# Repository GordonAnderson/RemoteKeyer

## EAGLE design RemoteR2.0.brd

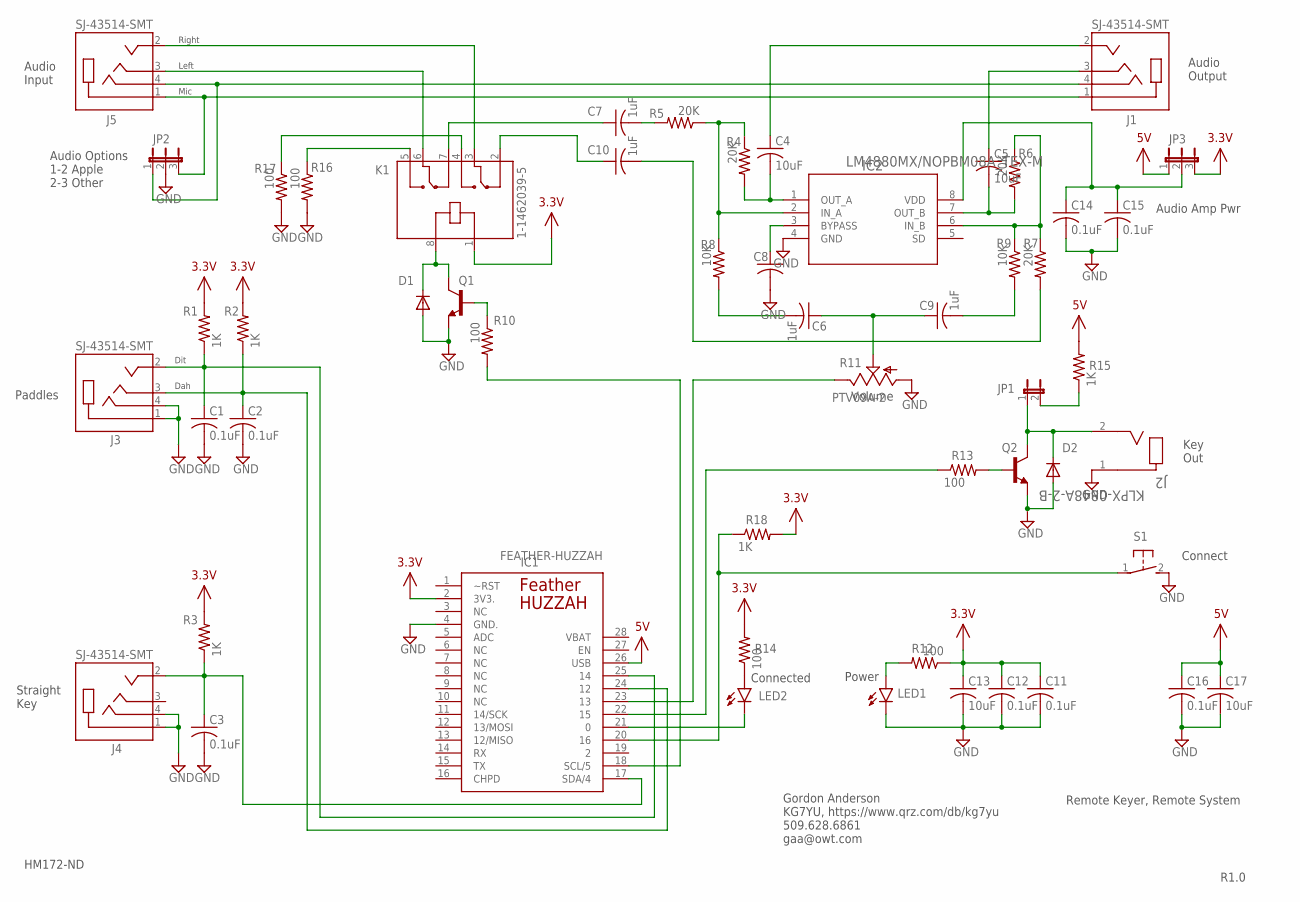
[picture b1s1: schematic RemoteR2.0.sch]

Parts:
C1, C2, C3, C11, C12, C14, C15, C16: 0.1uF; C0805
C4, C5: 10uF; C1206
C6, C7, C9, C10: 1uF; C0805
C8: C-USC0805; C0805
C13, C17: 10uF; C0805
D1, D2: DIODE-SOD323-R; SOD323-R
IC1: FEATHER-HUZZAH
IC2: LM4880MX/NOPBM08A_TEX-M; M08A_TEX-M
J1, J3, J4, J5: SJ-43514-SMT; CUI_SJ-43514-SMT
J2: KLPX-0848A-2-B; KLPX-0848A-2-B_KYC
JP1: JP1E; JP1
JP2, JP3: JP2E; JP2
K1: 1-1462039-5; RELAY_1-1462039-5
LED1, LED2: LED5MM
Q1, Q2: MMBT2369LT1-NPN-SOT23-BEC; SOT23-BEC
R1, R2, R3, R15, R18: 1K; R0805
R4, R5, R6, R7: 20K; R0805
R8, R9: 10K; R0805
R10, R12, R13, R14: 100; R0805
R11: PTV09A-2
R16, R17: 100; R1206
S1: 31-XX; B3F-31XX

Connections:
3.3V: C11.1, C12.1, C13.1, IC1.2 (3V3.), JP3.3, K1.1, R1.2, R2.2, R3.2, R12.1, R14.2, R18.2
5V: C16.1, C17.1, IC1.26 (USB), JP3.1, R15.2
CHPD: IC1.16 (CHPD)
GND: C1.2, C2.2, C3.2, C8.2, C11.2, C12.2, C13.2, C14.2, C15.2, C16.2, C17.2, D1.A, D2.A, IC1.4 (GND.), IC2.4 (GND), J2.1, J3.1 (SLEEVE), J3.4 (RING2), J4.1 (SLEEVE), J4.4 (RING2), JP2.2, LED1.K (C), Q1.E, Q2.E, R11.1 (A), R16.2, R17.2, S1.2 (S)
unnamed: Q2.B, R13.2
unnamed: C2.1, IC1.24 (12), J3.3 (RING1), R2.1
unnamed: C3.1, IC1.17 (SDA/4), J4.2 (TIP), R3.1
unnamed: C1.1, IC1.25 (14), J3.2 (TIP), R1.1
unnamed: C9.2, R9.2
unnamed: C4.2, IC2.1 (OUT_A), R4.2
unnamed: IC2.2 (IN_A), R4.1, R5.1, R8.1
unnamed: C8.1, IC2.3 (BYPASS)
unnamed: C7.1, K1.7
unnamed: C6.2, R8.2
unnamed: C5.2, IC2.7 (OUT_B), R6.2
unnamed: IC2.6 (IN_B), R6.1, R7.1, R9.1
unnamed: C6.1, C9.1, R11.2 (S)
unnamed: Q1.B, R10.1
unnamed: C4.1, J1.2 (TIP)
unnamed: C5.1, J1.3 (RING1)
unnamed: J5.3 (RING1), K1.6
unnamed: J5.2 (TIP), K1.3
unnamed: J1.1 (SLEEVE), J5.1 (SLEEVE), JP2.3
unnamed: C7.2, R5.2
unnamed: C10.1, K1.2
unnamed: C10.2, R7.2
unnamed: LED1.A, R12.2
unnamed: LED2.A, R14.1
unnamed: IC1.21 (0), LED2.K (C)
unnamed: IC1.23 (13), R11.3 (E)
unnamed: IC1.22 (15), R13.1
unnamed: IC1.18 (SCL/5), R10.2
unnamed: JP1.2, R15.1
unnamed: K1.4, R17.1
unnamed: K1.5, R16.1
unnamed: IC1.20 (16), R18.1, S1.1
unnamed: C14.1, C15.1, IC2.8 (VDD), JP3.2
unnamed: J1.4 (RING2), J5.4 (RING2), JP2.1
RELAY-: D2.C, J2.2, JP1.1, Q2.C
RELAY-1: D1.C, K1.8, Q1.C
VBAT: IC1.28 (VBAT)

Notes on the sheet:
Paddles
Straight Key
Right
Left
Mic
Dit
Dah
Power
Connected
Audio Input
Audio Output
Key Out
Volume
Remote Keyer, Remote System
R1.0
Connect
HM172-ND
Audio Amp Pwr
Audio Options 1-2 Apple 2-3 Other
Gordon Anderson KG7YU, https://www.qrz.com/db/kg7yu 509.628.6861 gaa@owt.com

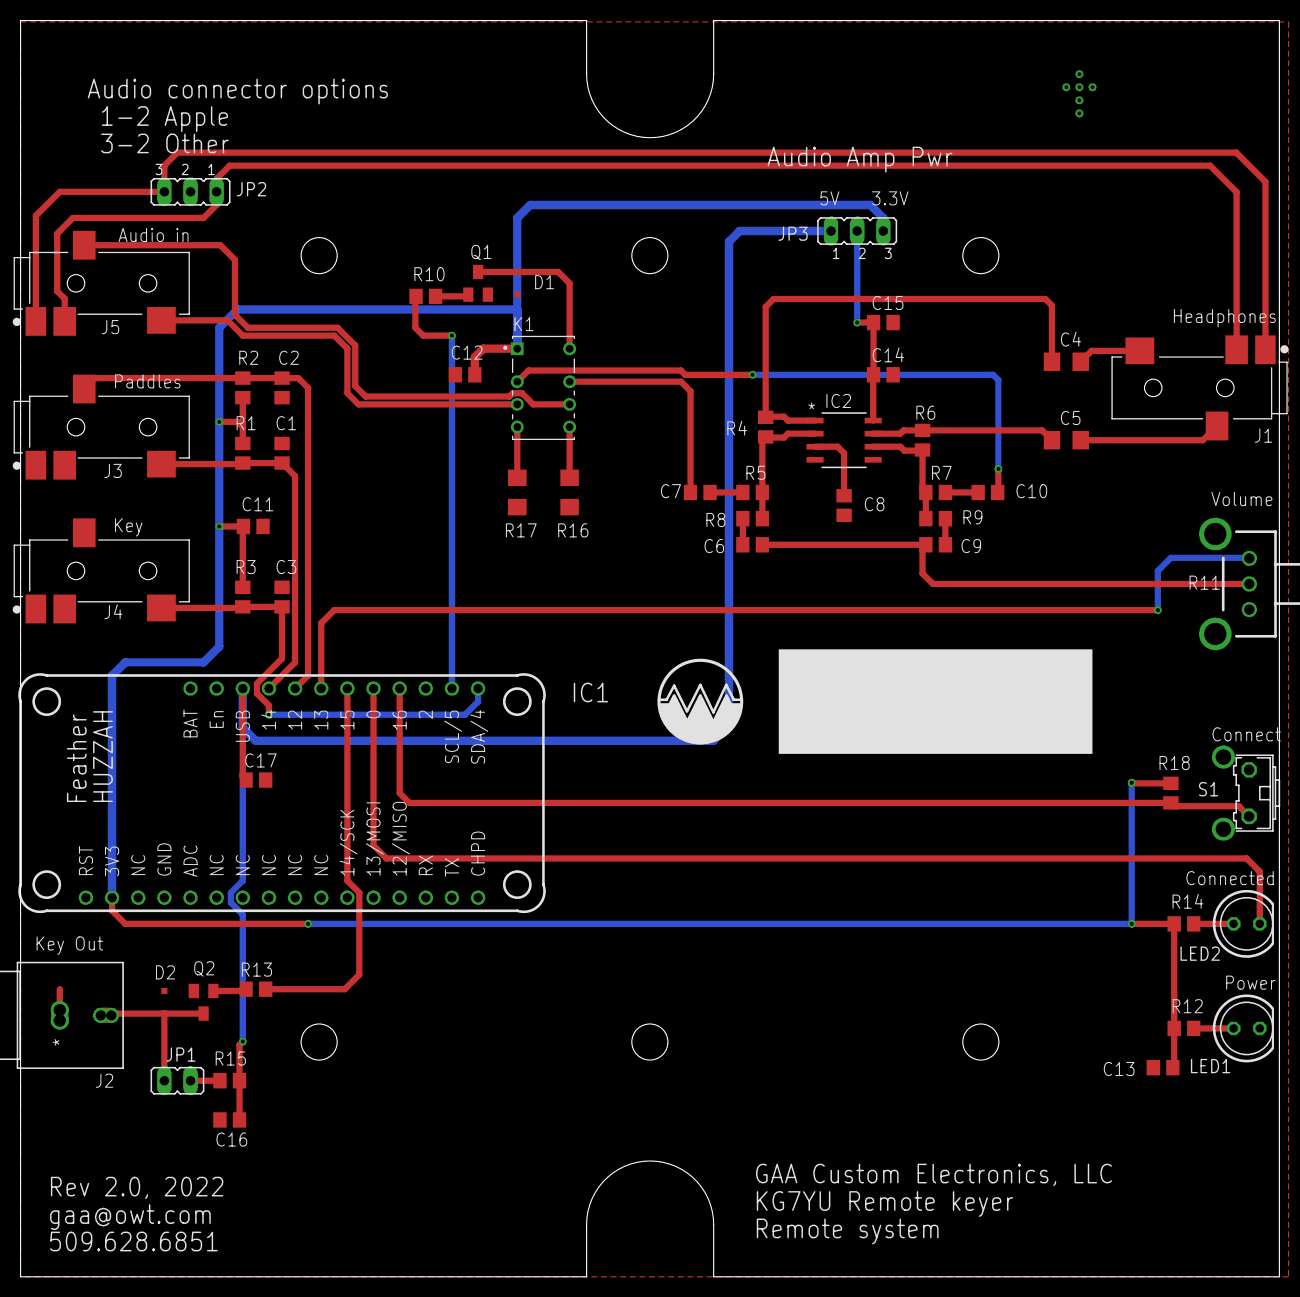
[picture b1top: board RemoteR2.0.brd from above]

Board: 2 copper layers, 122.3 x 122.0 mm, 54 parts (0 on the bottom side), 39 nets.

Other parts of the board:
U$1: LOGO2

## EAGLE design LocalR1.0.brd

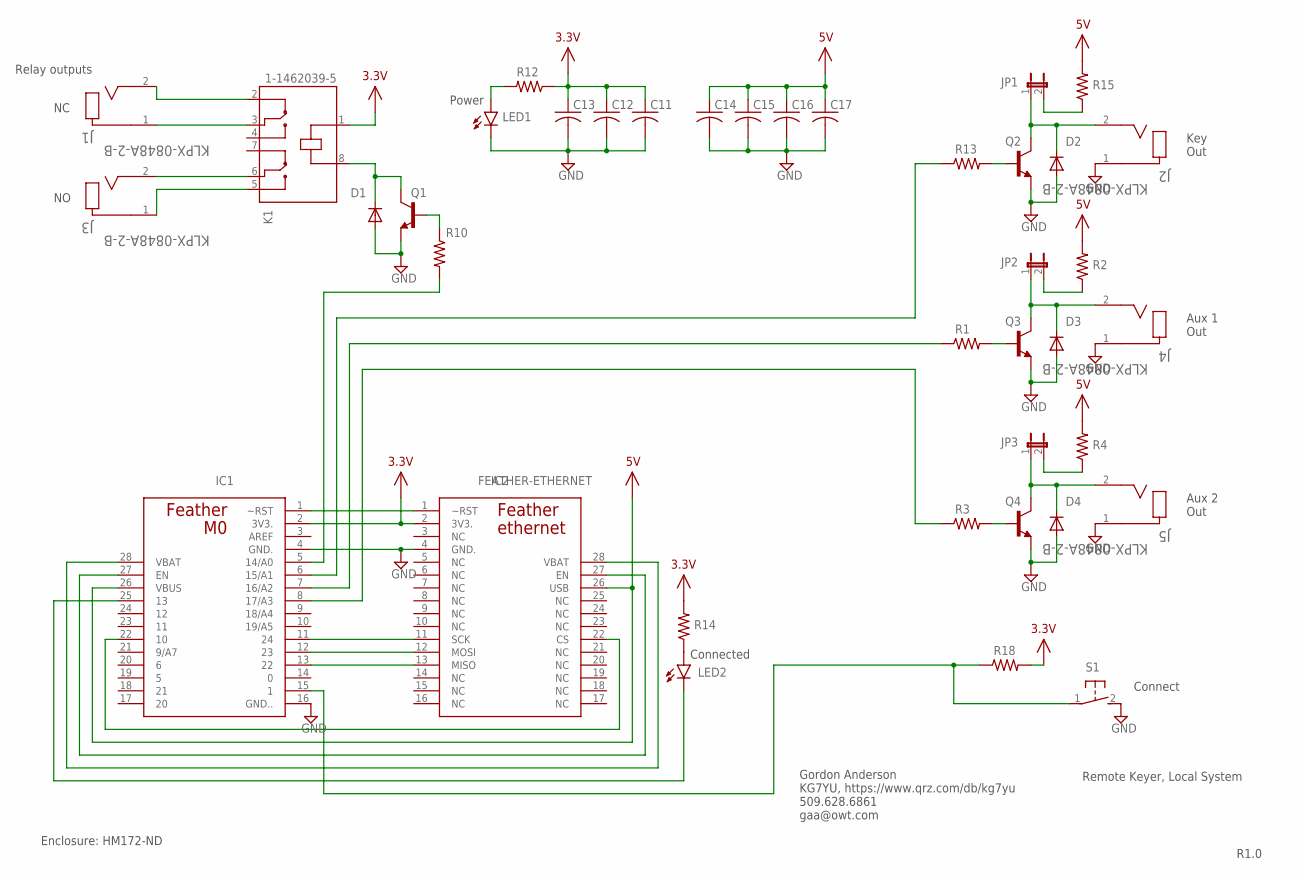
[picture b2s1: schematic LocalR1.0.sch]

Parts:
C11, C12, C13, C14, C15, C16, C17: C-USC0805; C0805
D1, D2, D3, D4: DIODE-SOD323-R; SOD323-R
IC1: FEATHER-M0
IC2: FEATHER-ETHERNET
J1, J2, J3, J4, J5: KLPX-0848A-2-B; KLPX-0848A-2-B_KYC
JP1, JP2, JP3: JP1E; JP1
K1: 1-1462039-5; RELAY_1-1462039-5
LED1, LED2: LED5MM
Q1, Q2, Q3, Q4: MMBT2369LT1-NPN-SOT23-BEC; SOT23-BEC
R1, R2, R3, R4, R10, R12, R13, R14, R15, R18: R-US_R0805; R0805
S1: 31-XX; B3F-31XX

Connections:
3.3V: C11.1, C12.1, C13.1, IC1.2 (3V3.), IC2.2 (3V3.), K1.1, R12.1, R14.2, R18.2
5V: C14.1, C15.1, C16.1, C17.1, IC1.26 (VBUS), IC2.26 (USB), R2.2, R4.2, R15.2
GND: C11.2, C12.2, C13.2, C14.2, C15.2, C16.2, C17.2, D1.A, D2.A, D3.A, D4.A, IC1.4 (GND.), IC1.16 (GND..), IC2.4 (GND.), J2.1, J4.1, J5.1, LED1.K (C), Q1.E, Q2.E, Q3.E, Q4.E, S1.2 (S)
unnamed: Q2.B, R13.2
unnamed: J1.1, K1.3
unnamed: J1.2, K1.2
unnamed: J3.2, K1.6
unnamed: J3.1, K1.5
unnamed: Q3.B, R1.2
unnamed: JP2.2, R2.1
unnamed: Q4.B, R3.2
unnamed: JP3.2, R4.1
unnamed: IC1.13 (22), IC2.13 (MISO)
unnamed: IC1.12 (23), IC2.12 (MOSI)
unnamed: IC1.11 (24), IC2.11 (SCK)
unnamed: IC1.1 (~RST), IC2.1 (~RST)
unnamed: Q1.B, R10.1
unnamed: IC1.15 (1), R18.1, S1.1
unnamed: IC1.22 (10), IC2.22 (CS)
unnamed: IC1.6 (15/A1), R13.1
unnamed: IC1.27 (EN), IC2.27 (EN)
unnamed: IC1.28 (VBAT), IC2.28 (VBAT)
unnamed: IC1.7 (16/A2), R1.1
unnamed: IC1.8 (17/A3), R3.1
unnamed: LED1.A, R12.2
unnamed: LED2.A, R14.1
unnamed: IC1.25 (13), LED2.K (C)
unnamed: IC1.5 (14/A0), R10.2
unnamed: JP1.2, R15.1
NC: IC2.16 (NC)
RELAY-: D2.C, J2.2, JP1.1, Q2.C
RELAY-1: D1.C, K1.8, Q1.C
RELAY-2: D3.C, J4.2, JP2.1, Q3.C
RELAY-3: D4.C, J5.2, JP3.1, Q4.C

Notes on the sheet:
Power
Connected
Key Out
Remote Keyer, Local System
R1.0
Connect
Enclosure: HM172-ND
Aux 1 Out
Aux 2 Out
Relay outputs
Gordon Anderson KG7YU, https://www.qrz.com/db/kg7yu 509.628.6861 gaa@owt.com

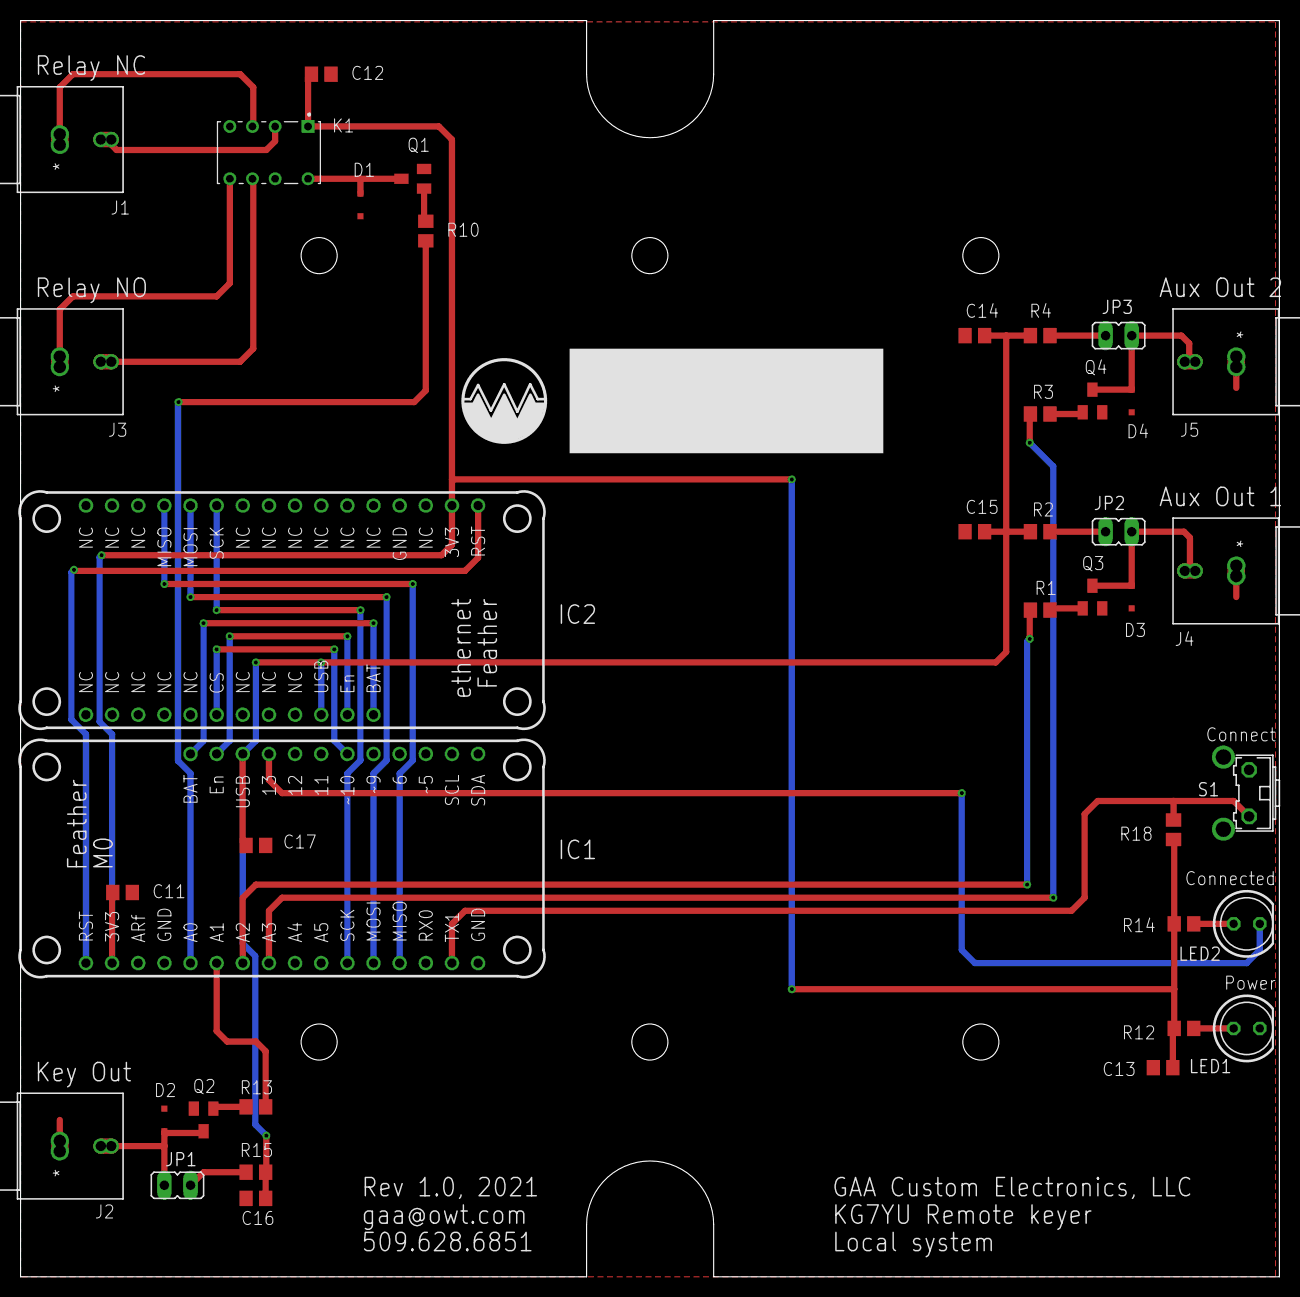
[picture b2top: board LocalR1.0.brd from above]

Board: 2 copper layers, 122.3 x 122.0 mm, 40 parts (0 on the bottom side), 33 nets.

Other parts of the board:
U$1: LOGO2

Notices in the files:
parts and their libraries:
COPYRIGHT: Copyright (C) 2021 Ultra Librarian. All rights reserved.
